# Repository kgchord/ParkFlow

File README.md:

# ParkFlow

FASTag (UHF RFID) + ANPR fusion on an on-site Edge Node for stop-free, token-free parking in India.
Vishwakarma Awards 2026-27, Stage 2 engineering package (prototype: the "ParkFlow Demo Lane").

**Status (25 Oct 2026): design stage. No hardware has been built or bench-tested yet.** Performance figures are targets or predictions to be bench-verified, unless a log in the repo shows a measured run. Billing goes to a mock NETC ledger; no real FASTag debit is attempted.

## Layout

| Folder | What is in it |
|---|---|
| `docs/` | Stage 1 concept, problem and journey, safety/FMEA, risks, roadmap, firmware notes, open decisions, references |
| `cad/openscad/` | Parametric OpenSCAD models (gantry, Edge Node enclosure, barrier, occupancy node, lane layout) |
| `cad/renders/`, `cad/dxf/`, `cad/stl/` | Preview renders, laser-cut profiles, printable parts |
| `cad/step/` | STEP interchange files generated by script from the same parameters |
| `cad/calcs/`, `cad/fea/` | Hand calculations and CalculiX/gmsh FEA decks, logs, figures |
| `cad/freecad/` | Rebuild guide and parameter spreadsheet generator for FreeCAD |
| `electronics/` | System design specification, pin map, KiCad schematic and placement-only PCB, ERC/DRC reports, diagrams |
| `firmware/` | Lane Controller (ESP32-S3) state machine and Edge Node fusion software, with host tests and logs |
| `bom/` | Priced bill of materials workbook (vendors in Delhi NCR, Bengaluru, Chennai, Mumbai) and notes |

## Reproduce

- Firmware tests: `./firmware/run_all.sh`
- FEA: `cad/fea/scripts/run_all.sh` (needs CalculiX and gmsh)
- STEP: `python3 cad/step/build_step.py` (needs CadQuery)

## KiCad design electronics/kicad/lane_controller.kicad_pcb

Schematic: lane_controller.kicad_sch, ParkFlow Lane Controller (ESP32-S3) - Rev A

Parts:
C1: 100uF 50V; CP_Elec_10x10.5
C2, C6, C13, C15, C19, C20, C22: 100nF; C_0603_1608Metric
C3, C4: 4.7uF 50V X7R; C_1210_3225Metric
C5: 6.8nF* (Cc); C_0603_1608Metric
C7, C8: 47uF 10V X5R; C_1210_3225Metric
C9: 10uF 10V; C_0805_2012Metric
C10, C11: 22uF 10V; C_0805_2012Metric
C12: 22uF; C_0805_2012Metric
C14: 1uF; C_0603_1608Metric
C18, C30, C31, C32, C33, C34, C35, C36: 10nF; C_0603_1608Metric
C21: 470uF 10V (LED bulk); CP_Elec_8x10
D1: BZT52C15 (Vgs clamp); D_SOD-123
D2: SMBJ33A; D_SMB
D3: B560C (60V 5A); D_SMC
D4: SS14 (VBUS OR); D_SMA
D5: BAT54W; D_SOD-323
D6: GREEN 0603 (3V3 OK); LED_0603_1608Metric
D7: SM712; SOT-23
D9: BAT54S (ADC clamp); SOT-23
D10, D11, D12, D13, D14, D15: 1N4148W (rev.); D_SOD-123
D16: S1M (coil flyback); D_SMA
D17: 1N4148W; D_SOD-123
D18: SS14 (5V OR); D_SMA
F1: 3A NANO2 0451003.MRL (very fast-acting); Fuse_Littelfuse-NANO2-451_453
F2: MF-R075 (0.75A hold, 60V); Fuse_Bourns_MF-RG500
J1: 24V_LOGIC_IN; TerminalBlock_Phoenix_MKDS-3-2-5.08_1x02_P5.08mm_Horizontal
J4: E-STOP NC LOOP + K1 COIL; TerminalBlock_Phoenix_MKDS-3-4-5.08_1x04_P5.08mm_Horizontal
J5: FIELD I/O 8P; TerminalBlock_Phoenix_MKDS-3-8-5.08_1x08_P5.08mm_Horizontal
J6: PSU/UPS STATUS (AC-OK, BAT-OK dry contacts to +24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; TerminalBlock_Phoenix_MKDS-3-3-5.08_1x03_P5.08mm_Horizontal
J7: RS485 RFID (A,B,0V); TerminalBlock_Phoenix_MKDS-3-3-5.08_1x03_P5.08mm_Horizontal
J8: BUZZER 24V (+, -); TerminalBlock_Phoenix_MKDS-3-2-5.08_1x02_P5.08mm_Horizontal
J9: HUB12 2x8 IDC (verify vs P10 silkscreen); IDC-Header_2x08_P2.54mm_Vertical
J10: WS2812 JST-XH 3P (B3B-XH-A); JST_XH_B3B-XH-A_1x03_P2.50mm_Vertical
J11: EDGE LINK JST-XH 5P (B5B-XH-A); JST_XH_B5B-XH-A_1x05_P2.50mm_Vertical
J12: USB-C 16P (GCT USB4105-GF-A); USB_C_Receptacle_GCT_USB4105-xx-A_16P_TopMnt_Horizontal
J13: P10 SIGN POWER 5V/3A; TerminalBlock_Phoenix_MKDS-3-2-5.08_1x02_P5.08mm_Horizontal
J14: IBT-2 LOGIC 1x8 (RPWM,LPWM,R_EN,L_EN,R_IS,L_IS,VC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; PinHeader_1x08_P2.54mm_Vertical
JP1: TERM EN; PinHeader_1x02_P2.54mm_Vertical
L1: 6.8uH Isat>=7A*; L_12x12mm_H8mm
L2: 2.2uH 3A; L_Taiyo-Yuden_NR-40xx
Q1: FQD11P06 (-60V P-FET)*; TO-252-2
Q2, Q3: 2N7002; SOT-23
Q4: IRLML0060TRPBF (60V); SOT-23
Q5: IRLML0060TRPBF; SOT-23
R1, R3, R8, R15, R16, R41, R45, R49, R53, R57, R61, R83: 10k; R_0603_1608Metric
R2, R10, R19, R20, R30, R31, R32, R78, R81: 100k; R_0603_1608Metric
R4: 200k (fsw 500 kHz); R_0603_1608Metric
R5: 10k* (Rc); R_0603_1608Metric
R6: 100k (EN/UVLO upper); R_0603_1608Metric
R7: 53.6k (Vout=5.09V); R_0603_1608Metric
R9: 453k; R_0603_1608Metric
R11, R12: 5.1k; R_0603_1608Metric
R13, R14: 22R; R_0603_1608Metric
R17, R18, R77, R80: 100R; R_0603_1608Metric
R21, R29: 1k; R_0603_1608Metric
R22: 10k (DE pull-down); R_0603_1608Metric
R23, R24: 680R fail-safe bias (DNP); R_0603_1608Metric
R25: 120R term; R_0603_1608Metric
R28: 1k* R_IS (DNP: the IBT-2 module already has 1k on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; R_0603_1608Metric
R40, R44, R48, R52, R56, R60, R82: 4.7k 1206; R_1206_3216Metric
R64: 10k (OE pull-up: sign off at reset); R_0603_1608Metric
R70, R71, R72, R73, R74, R75: 33R; R_0603_1608Metric
R76: 330R; R_0603_1608Metric
R90: 10k (EN/UVLO lower, UVLO ~13 V); R_0603_1608Metric
R91: 100R (IS_A isolation); R_0603_1608Metric
R92: 100R (IS_B isolation); R_0603_1608Metric
R93: 10k (unused A7 tie); R_0603_1608Metric
SW1: BOOT; SW_SPST_TL3342
SW2: RESET; SW_SPST_TL3342
U1: TPS54560BDDA; TI_SO-PowerPAD-8_ThermalVias
U2: TLV62569DBVR; SOT-23-5
U3: USBLC6-2SC6; SOT-23-6
U4: ESP32-S3-WROOM-1-N16R8; ESP32-S3-WROOM-1
U5: TPS3823-33DBVR (WDT 1.6 s); SOT-23-5
U6: THVD1450DR; SOIC-8_3.9x4.9mm_P1.27mm
U9: 74AHCT1G08 (R_EN = L_EN = MOT_EN & ESTOP_OK, 5 V 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; SOT-23-5
U10: 74AHCT1G08 (LPWM = CLOSE only if BEAM_CLEAR); SOT-23-5
U11, U12, U13, U14, U15, U16, U17: EL817S1(C) / PC817; SMDIP-4_W9.53mm
U18: SN74HCT245PWR (5 V, TTL inputs); TSSOP-20_4.4x6.5mm_P0.65mm
U19: 74AHCT1G08 (RPWM = OPEN request & ESTOP_OK); SOT-23-5

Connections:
/+3V3: C10.1, C11.1, C12.1, C13.1, C15.1, D9.2 (K), L2.2, R9.1, R15.1, R16.1, R21.1, R23.1, R64.2, U4.2 (3V3), U5.3 (~MR), U5.5 (VDD), U6.8 (VCC), U11.4, U12.4, U13.4, U14.4, U15.4, U16.4, U17.4
/+5V: C7.1, C8.1, C19.1, C20.1, C21.1, C22.1, D18.2 (A), J10.1, J13.1, J14.7, L1.2, R7.1, U9.5 (VCC), U10.5 (VCC), U18.1 (A->B), U18.20 (VCC), U19.5 (VCC)
/+5V_LOGIC: C9.1, D4.1 (K), D18.1 (K), U2.1 (EN), U2.4 (VIN)
/+24V: C1.1, C3.1, C4.1, D1.1 (K), D2.2 (A2), F2.1, Q1.3 (S), R2.1, R6.1, U1.2 (VIN)
/+24V_FIELD: D17.1 (K), F2.2, J4.1, J5.1, J5.7, J6.3, J8.1
/AC_OK: C34.1, R57.1, U4.21 (IO13), U15.3
/BAT_OK: C35.1, R61.1, U4.38 (IO2), U16.3
/BEAM_CLEAR: C32.1, R49.1, U4.19 (IO11), U10.2, U13.3
/BUZ_CTRL: R77.1, U4.11 (IO18)
/BUZ_G: Q5.1 (G), R77.2, R78.1
/BUZ_LO: D17.2 (A), J8.2, Q5.3 (D)
/EDGE_RX: R18.1, U4.36 (RXD0)
/EDGE_TX: R17.1, U4.37 (TXD0)
/ESP_EN: C14.1, D5.2 (A), Q2.3 (D), R15.2, SW2.1, U4.3 (EN)
/ESTOP_LOOP: D16.1 (K), J4.2, J4.3, R82.1
/ESTOP_OK: C36.1, R83.1, U4.12 (IO8), U9.2, U17.3, U19.2
/GND: C1.2, C2.2, C3.2, C4.2, C5.2, C7.2, C8.2, C9.2, C10.2, C11.2, C12.2, C13.2, C14.2, C15.2, C18.2, C19.2, C20.2, C21.2, C22.2, C30.2, C31.2, C32.2, C33.2, C34.2, C35.2, C36.2, D2.1 (A1), D3.2 (A), D6.1 (K), D7.3 (common), D9.1 (A), D10.2 (A), D11.2 (A), D12.2 (A), D13.2 (A), D14.2 (A), D15.2 (A), J1.2, J5.2, J5.8, J7.3, J9.3, J9.5, J9.7, J9.9, J9.11, J9.13, J9.15, J10.3, J11.1, J12.A1 (GND), J12.A12 (GND), J12.B1 (GND), J12.B12 (GND), J12.S1 (SHIELD), J13.2, J14.8, Q2.2 (S), Q3.2 (S), Q4.2 (S), Q5.2 (S), R1.2, R3.2, R4.2, R8.2, R10.2, R11.2, R12.2, R19.2, R20.2, R22.2, R24.2, R28.2, R30.2, R31.2, R32.2, R41.2, R45.2, R49.2, R53.2, R57.2, R61.2, R78.2, R81.2, R83.2, R90.2, R93.2, SW1.2, SW2.2, U1.7 (GND), U1.9 (GND), U2.2 (GND), U3.2 (GND), U4.1 (GND), U4.40 (GND), U4.41 (GND), U5.2 (GND), U6.5 (GND), U9.3 (GND), U10.3 (GND), U11.2, U12.2, U13.2, U14.2, U15.2, U16.2, U17.2, U18.10 (GND), U18.19 (CE), U19.3 (GND)
/GPIO0_BOOT: Q3.3 (D), R16.2, SW1.1, U4.27 (IO0)
/GPIO19_USB_DN: R14.2, U4.13 (IO19)
/GPIO20_USB_DP: R13.2, U4.14 (IO20)
/HUB_A: J9.2, R70.2
/HUB_A_3V3: U4.31 (IO38), U18.2 (A0)
/HUB_A_5: R70.1, U18.18 (B0)
/HUB_B: J9.4, R71.2
/HUB_B_3V3: U4.32 (IO39), U18.3 (A1)
/HUB_B_5: R71.1, U18.17 (B1)
/HUB_CLK: J9.8, R72.2
/HUB_CLK_3V3: U4.33 (IO40), U18.4 (A2)
/HUB_CLK_5: R72.1, U18.16 (B2)
/HUB_LAT: J9.10, R73.2
/HUB_LAT_3V3: U4.34 (IO41), U18.5 (A3)
/HUB_LAT_5: R73.1, U18.15 (B3)
/HUB_OE: J9.1, R74.2
/HUB_OE_3V3: R64.1, U4.35 (IO42), U18.6 (A4)
/HUB_OE_5: R74.1, U18.14 (B4)
/HUB_R: J9.12, R75.2
/HUB_R_3V3: U4.24 (IO47), U18.7 (A5)
/HUB_R_5: R75.1, U18.13 (B5)
/IN_ACOK: J6.1, R56.1
/IN_BATOK: J6.2, R60.1
/IN_BEAM: J5.5, R48.1
/IN_LIM_DN: J5.4, R44.1
/IN_LIM_UP: J5.3, R40.1
/IN_PRES: J5.6, R52.1
/IS_A: J14.5, R91.1
/IS_B: J14.6, R92.1
/J11_RX: J11.3, R18.2
/J11_TX: J11.2, R17.2
/K1_COIL_LO: D16.2 (A), J4.4, Q4.3 (D)
/K1_EN: R80.1, U4.25 (IO48)
/K1_G: Q4.1 (G), R80.2, R81.1
/LED_PWR_A: D6.2 (A), R21.2
/LIM_DN_OK: C31.1, R45.1, U4.18 (IO10), U12.3
/LIM_UP_OK: C30.1, R41.1, U4.17 (IO9), U11.3
/MOT_EN_MCU: R30.1, U4.7 (IO7), U9.1
/MOT_INH: J14.3, J14.4, U9.4
/MOT_IN_A: R32.1, U4.5 (IO5), U19.1
/MOT_IN_B_MCU: R31.1, U4.6 (IO6), U10.1
/MOT_IS: R28.1, R29.1, R91.2, R92.2
/MOT_ISENSE: C18.1, D9.3 (COM), R29.2, U4.39 (IO1)
/MOT_LPWM: J14.2, U10.4
/MOT_RPWM: J14.1, U19.4
/OPTO0_A: D10.1 (K), R40.2, U11.1
/OPTO1_A: D11.1 (K), R44.2, U12.1
/OPTO2_A: D12.1 (K), R48.2, U13.1
/OPTO3_A: D13.1 (K), R52.2, U14.1
/OPTO4_A: D14.1 (K), R56.2, U15.1
/OPTO5_A: D15.1 (K), R60.2, U16.1
/OPTO6_A: R82.2, U17.1
/PI_BOOT_CTRL: J11.5, Q3.1 (G), R20.1
/PI_EN_CTRL: J11.4, Q2.1 (G), R19.1
/PRESENCE: C33.1, R53.1, U4.20 (IO12), U14.3
/Q1_G: D1.2 (A), Q1.1 (G), R1.1
/RS485_A: D7.1 (A1), J7.1, R23.2, R25.1, U6.6 (A)
/RS485_B: D7.2 (A2), J7.2, JP1.2 (B), R24.1, U6.7 (B)
/RS485_DE: R22.1, U4.10 (IO17), U6.2 (~RE), U6.3 (DE)
/RS485_DI: U4.8 (IO15), U6.4 (DI)
/RS485_RO: U4.9 (IO16), U6.1 (RO)
/RS485_TERM: JP1.1 (A), R25.2
/U1_BOOT: C6.1, U1.1 (BOOT)
/U1_CC: C5.1, R5.2
/U1_COMP: R5.1, U1.6 (COMP)
/U1_EN: R6.2, R90.1, U1.3 (EN)
/U1_FB: R7.2, R8.1, U1.5 (FB)
/U1_RT: R4.1, U1.4 (RT/CLK)
/U1_SW: C6.2, D3.1 (K), L1.1, U1.8 (SW)
/U2_FB: R9.2, R10.1, U2.5 (FB)
/U2_SW: L2.1, U2.3 (SW)
/U18_A7_TIE: R93.1, U18.9 (A7)
/USB_CC1: J12.A5 (CC1), R11.1
/USB_CC2: J12.B5 (CC2), R12.1
/USB_DN: R14.1, U3.4 (I/O2)
/USB_DN_C: J12.A7 (D-), J12.B7 (D-), U3.3 (I/O2)
/USB_DP: R13.1, U3.6 (I/O1)
/USB_DP_C: J12.A6 (D+), J12.B6 (D+), U3.1 (I/O1)
/V24_SENSE: C2.1, R2.2, R3.1, U4.4 (IO4)
/VBUS: D4.2 (A), J12.A4 (VBUS), J12.A9 (VBUS), J12.B4 (VBUS), J12.B9 (VBUS), U3.5 (VBUS)
/VIN_F: F1.2, Q1.2 (D)
/VIN_RAW: F1.1, J1.1
/WDT_RST_N: D5.1 (K), U5.1 (~RESET)
/WDT_WDI: U4.22 (IO14), U5.4 (WDI)
/WS2812_3V3: U4.23 (IO21), U18.8 (A6)
/WS2812_5: R76.1, U18.12 (B6)
/WS2812_DOUT: J10.2, R76.2

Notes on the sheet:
1. 24 V INPUT PROTECTION (fuse, reverse-polarity P-FET, TVS)
2. 24 V -> 5 V BUCK (TPS54560, 5 A)
3. 5 V -> 3.3 V BUCK (TLV62569, 2 A) + USB-C
4. ESP32-S3-WROOM-1-N16R8 + RESET / BOOT / WATCHDOG / EDGE LINK
5. RS485 TO UHF RFID READER (THVD1450 + SM712)
6. H-BRIDGE: IBT-2 (BTS7960) MODULE HEADER + hardware interlocks (74AHCT1G08 @ 5 V)
7. OPTO-ISOLATED 24 V INPUTS (active-high: 24 V at the terminal = LED on = output HIGH)
8. E-STOP LOOP + CONTACTOR COIL DRIVER (firmware-independent motor cut)
9. HUB12 (P10) + WS2812 LEVEL SHIFT (74HCT245 @5 V), BUZZER
10. FIELD CONNECTORS (5.08 mm fixed screw terminals / JST-XH)
Notes: (a) Symbol MAX481E used for THVD1450DR (identical 8-pin RS485 pinout). (b) TLV62568DBV symbol used for TLV62569DBVR (same pinout). (c) 74LS245 symbol used for SN74HCT245PWR and 74LVC1G08 symbol used for the 74AHCT1G08 gates U9/U10/U19 (same pinout). (d) K1 is the external DIN contactor LC1D0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
K1 = external DIN contactor Schneider LC1D09BD (24 VDC coil); its contacts switch the +24V line to the IBT-2 module B+ (off this PCB). E-stop (BOM: ProMax 22 mm 2-pole, contacts 1 A DC) NC contact in series with the coil supply: pressing it de-energises K1 and removes motor power regardless of firm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
J5: limit switches (BOM: ME-8108) wired on the NC contact between +24V_FIELD (J5.1) and IN_LIM_x (open = limit reached or wire break -> LOW -> safe); confirm the NC terminal on the real part. IN_BEAM: the BOM through-beam receiver (Delta PS-MT5 series, PNP) drives 24 V onto IN_BEAM when the beam is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

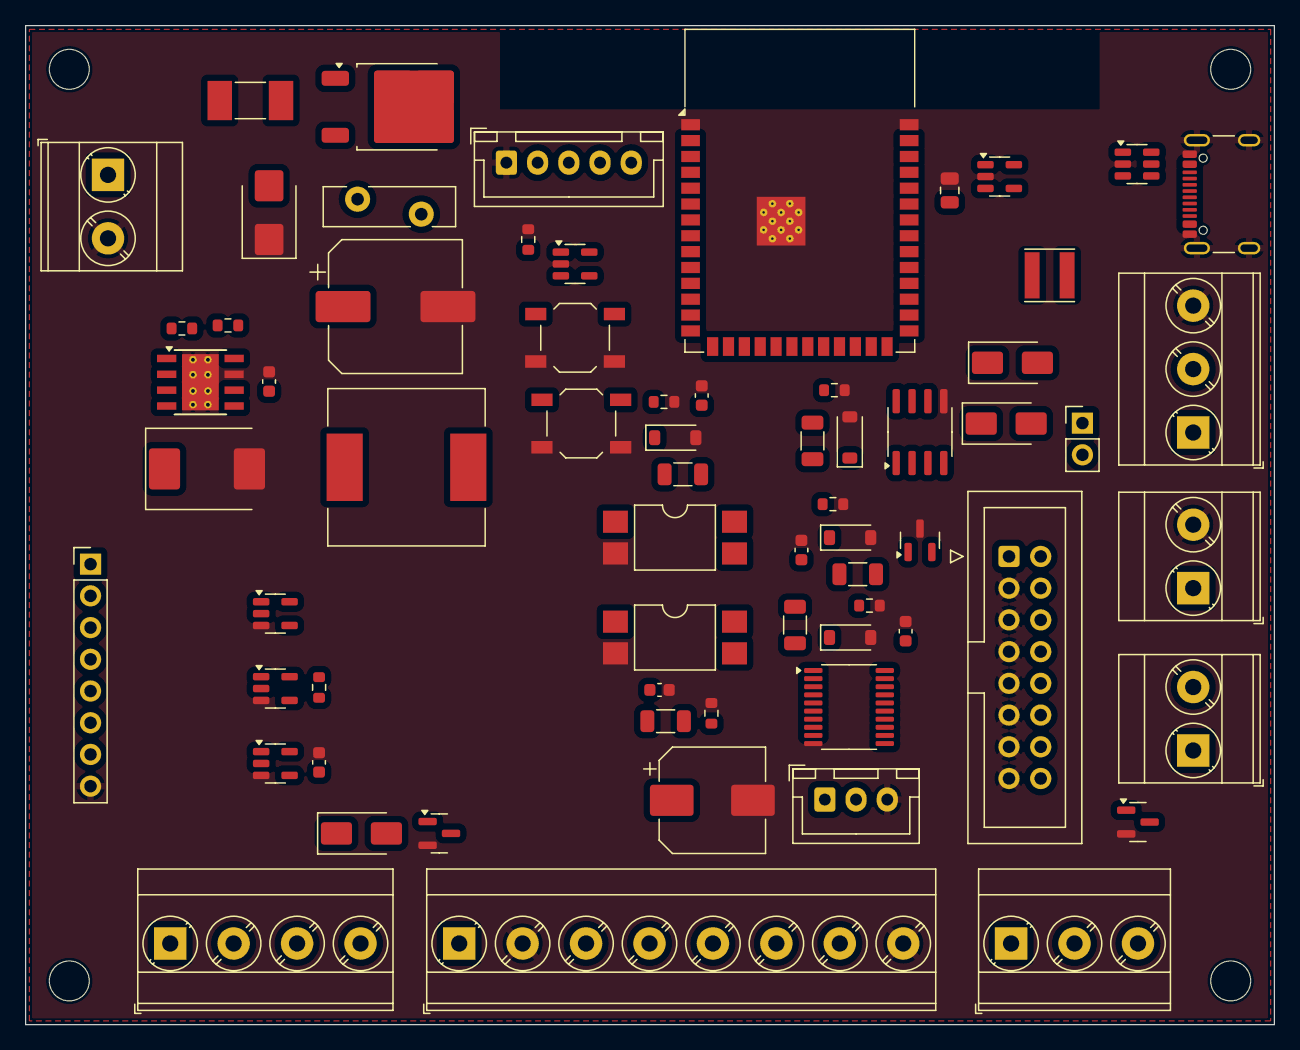
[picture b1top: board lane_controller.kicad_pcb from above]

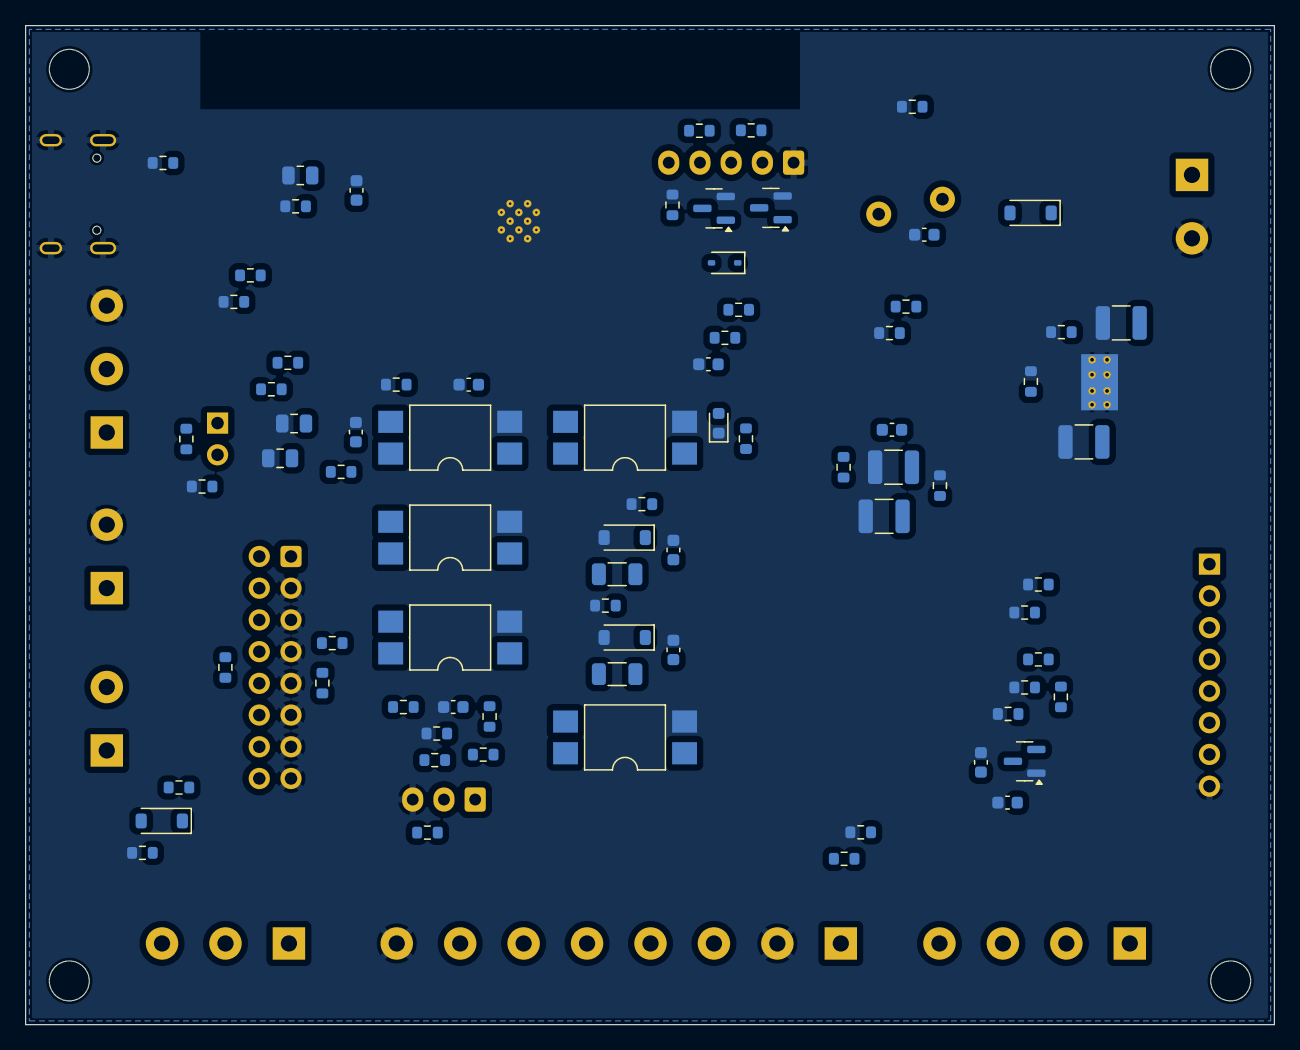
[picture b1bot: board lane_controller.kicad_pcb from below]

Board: 2 copper layers, 100.0 x 80.0 mm, 149 parts (78 on the bottom side), 104 nets, no tracks yet.

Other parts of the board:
H1, H2, H3, H4: M3; MountingHole_3.2mm_M3

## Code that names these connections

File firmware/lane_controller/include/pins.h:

// ESP32-S3-WROOM-1 pin assignment for the ParkFlow Lane Controller (Rev A).
// SOURCE OF TRUTH: electronics/tools/gen_lane_controller_sch.py, dict `esp`.
// If the schematic changes, change this file (test_pins in the host suite
// cross-checks the table below against itself for duplicates only; it cannot
// read the Python script).
#pragma once
namespace pf {
namespace pins {
constexpr int BOOT_BTN   = 0;   // GPIO0_BOOT  (also used as RE-ARM button after boot, see FIRMWARE.md)
constexpr int MOT_ISENSE = 1;   // ADC1_CH0, IBT-2 module R_IS/L_IS via R91/R92 100R + R29 1k + clamp
constexpr int BAT_OK     = 2;   // opto in, UPS battery OK (HIGH = ok)
constexpr int V24_SENSE  = 4;   // ADC1_CH3, 100k/10k divider on +24V
constexpr int MOT_IN_A   = 5;   // H-bridge half A IN (OPEN drive)
constexpr int MOT_IN_B   = 6;   // H-bridge half B IN (CLOSE drive); PCB gates it with BEAM_CLEAR (U10)
constexpr int MOT_EN     = 7;   // H-bridge INH request; PCB ANDs it with ESTOP_OK (U9)
constexpr int ESTOP_OK   = 8;   // opto in, HIGH = E-stop loop healthy
constexpr int LIM_UP_OK  = 9;   // opto in, NC switch: HIGH = NOT at limit, LOW = reached or wire break
constexpr int LIM_DN_OK  = 10;  // same polarity as LIM_UP_OK
constexpr int BEAM_CLEAR = 11;  // opto in, HIGH = beam clear (light-ON receiver); LOW = broken or cable cut
constexpr int PRESENCE   = 12;  // opto in, HIGH = occupied (ASSUMED: sensor type not fixed by schematic)
constexpr int AC_OK      = 13;  // opto in, HIGH = mains OK (PSU relay closed)
constexpr int WDT_WDI    = 14;  // TPS3823-33 WDI, toggled to kick external watchdog (1.6 s)
constexpr int RS485_DI   = 15;  // ESP TX -> THVD1450 DI
constexpr int RS485_RO   = 16;  // ESP RX <- THVD1450 RO
constexpr int RS485_DE   = 17;  // DE and /RE tied together
constexpr int BUZ_CTRL   = 18;  // 24 V piezo, low-side MOSFET, HIGH = sound
constexpr int USB_DN     = 19;  // native USB (programming)
constexpr int USB_DP     = 20;
constexpr int WS2812     = 21;  // status RGB LED (via 74HCT245 level shift)
constexpr int HUB_A      = 38;  // HUB12 via 74HCT245
constexpr int HUB_B      = 39;
constexpr int HUB_CLK    = 40;
constexpr int HUB_LAT    = 41;
constexpr int HUB_OE     = 42;  // R64 pull-up: sign blanked at reset
constexpr int HUB_R      = 47;  // HUB12 data
constexpr int K1_EN      = 48;  // contactor coil driver, HIGH = energise K1 (motor power on)
constexpr int EDGE_TX    = 43;  // UART0 TXD0 -> Edge Node (R17 100R)
constexpr int EDGE_RX    = 44;  // UART0 RXD0 <- Edge Node (R18 100R)
}  // namespace pins
}  // namespace pf

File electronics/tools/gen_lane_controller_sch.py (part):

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P('Device', 'D_Schottky', 'D4', 'SS14 (VBUS OR)', (150, 290), {'A': 'VBUS', 'K': '+5V_LOGIC'}, fp='Diode_SMD:D_SMA')
P('Device', 'D_Schottky', 'D18', 'SS14 (5V OR)', (150, 275), {'A': '+5V', 'K': '+5V_LOGIC'}, fp='Diode_SMD:D_SMA')
P('power', 'PWR_FLAG', '#FLG05', 'PWR_FLAG', (185, 230), {'1': '+5V_LOGIC'})
R('R13', '22R', (170, 300), 'USB_DP', 'GPIO20_USB_DP', rot=90)
R('R14', '22R', (170, 312), 'USB_DN', 'GPIO19_USB_DN', rot=90)

# ------------------------------------------------------------------ 4. ESP32-S3
esp = {
    '3V3': '+3V3', 'GND': 'GND', 'EN': 'ESP_EN',
    'IO0': 'GPIO0_BOOT', 'IO1': 'MOT_ISENSE', 'IO2': 'BAT_OK', 'IO3': 'NC', 'IO4': 'V24_SENSE',
    'IO5': 'MOT_IN_A', 'IO6': 'MOT_IN_B_MCU', 'IO7': 'MOT_EN_MCU', 'IO8': 'ESTOP_OK', 'IO9': 'LIM_UP_OK',
    'IO10': 'LIM_DN_OK', 'IO11': 'BEAM_CLEAR', 'IO12': 'PRESENCE', 'IO13': 'AC_OK', 'IO14': 'WDT_WDI',
    'IO15': 'RS485_DI', 'IO16': 'RS485_RO', 'IO17': 'RS485_DE', 'IO18': 'BUZ_CTRL',
    'IO19': 'GPIO19_USB_DN', 'IO20': 'GPIO20_USB_DP', 'IO21': 'WS2812_3V3',
    'IO35': 'NC', 'IO36': 'NC', 'IO37': 'NC',
    'IO38': 'HUB_A_3V3', 'IO39': 'HUB_B_3V3', 'IO40': 'HUB_CLK_3V3', 'IO41': 'HUB_LAT_3V3', 'IO42': 'HUB_OE_3V3',
    'IO45': 'NC', 'IO46': 'NC', 'IO47': 'HUB_R_3V3', 'IO48': 'K1_EN',
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C('C13', '100nF', (312, 55), '+3V3', 'GND')
R('R15', '10k', (270, 60), '+3V3', 'ESP_EN')
C('C14', '1uF', (270, 85), 'ESP_EN', 'GND')
R('R16', '10k', (270, 110), '+3V3', 'GPIO0_BOOT')
P('Switch', 'SW_Push', 'SW1', 'BOOT', (270, 135), {'1': 'GPIO0_BOOT', '2': 'GND'}, fp='Button_Switch_SMD:SW_SPST_TL3342')
P('Switch', 'SW_Push', 'SW2', 'RESET', (270, 150), {'1': 'ESP_EN', '2': 'GND'}, fp='Button_Switch_SMD:SW_SPST_TL3342')
# external watchdog TPS3823-33 (WDI 1.6 s): RESET pulls EN low through Schottky (diode-OR with RC / Pi)
P('ParkFlow', 'TPS3823-33', 'U5', 'TPS3823-33DBVR (WDT 1.6 s)', (420, 60),
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R('R17', '100R', (420, 110), 'EDGE_TX', 'J11_TX', rot=90)
R('R18', '100R', (420, 125), 'EDGE_RX', 'J11_RX', rot=90)
P('Device', 'Q_NMOS_GSD', 'Q2', '2N7002', (430, 150), {'G': 'PI_EN_CTRL', 'S': 'GND', 'D': 'ESP_EN'}, fp='Package_TO_SOT_SMD:SOT-23')
P('Device', 'Q_NMOS_GSD', 'Q3', '2N7002', (460, 150), {'G': 'PI_BOOT_CTRL', 'S': 'GND', 'D': 'GPIO0_BOOT'}, fp='Package_TO_SOT_SMD:SOT-23')
R('R19', '100k', (430, 180), 'PI_EN_CTRL', 'GND')
R('R20', '100k', (460, 180), 'PI_BOOT_CTRL', 'GND')
P('Connector_Generic', 'Conn_01x05', 'J11', 'EDGE LINK JST-XH 5P (B5B-XH-A)', (470, 110),
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R('R23', '680R fail-safe bias (DNP)', (345, 245), '+3V3', 'RS485_A')
R('R24', '680R fail-safe bias (DNP)', (345, 290), 'RS485_B', 'GND')
R('R25', '120R term', (365, 268), 'RS485_A', 'RS485_TERM')
P('Jumper', 'Jumper_2_Open', 'JP1', 'TERM EN', (390, 268), {'A': 'RS485_TERM', 'B': 'RS485_B'}, fp='Connector_PinHeader_2.54mm:PinHeader_1x02_P2.54mm_Vertical')
P('Diode', 'SM712_SOT23', 'D7', 'SM712', (420, 268), {'A1': 'RS485_A', 'A2': 'RS485_B', 'common': 'GND'}, fp='Package_TO_SOT_SMD:SOT-23')
P('Connector', 'Screw_Terminal_01x03', 'J7', 'RS485 RFID (A,B,0V)', (460, 268),
  {'1': 'RS485_A', '2': 'RS485_B', '3': 'GND'}, fp='TerminalBlock_Phoenix:TerminalBlock_Phoenix_MKDS-3-3-5.08_1x03_P5.08mm_Horizontal')
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P('Connector_Generic', 'Conn_01x08', 'J14', 'IBT-2 LOGIC 1x8 (RPWM,LPWM,R_EN,L_EN,R_IS,L_IS,VCC,GND)', (530, 60),
  {'1': 'MOT_RPWM', '2': 'MOT_LPWM', '3': 'MOT_INH', '4': 'MOT_INH', '5': 'IS_A', '6': 'IS_B', '7': '+5V', '8': 'GND'},
  fp='Connector_PinHeader_2.54mm:PinHeader_1x08_P2.54mm_Vertical')
R('R28', '1k* R_IS (DNP: the IBT-2 module already has 1k on each IS pin)', (640, 175), 'MOT_IS', 'GND', )
R('R91', '100R (IS_A isolation)', (600, 160), 'IS_A', 'MOT_IS', rot=90)
R('R92', '100R (IS_B isolation)', (600, 172), 'IS_B', 'MOT_IS', rot=90)
R('R29', '1k', (660, 160), 'MOT_IS', 'MOT_ISENSE', rot=90)
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R('R81', '100k', (130, 415), 'K1_G', 'GND')
# E-stop healthy sense (fail-safe: loop broken -> ESTOP_OK low)
R('R82', '4.7k 1206', (150, 365), 'ESTOP_LOOP', 'OPTO6_A', fp='Resistor_SMD:R_1206_3216Metric')
P('Isolator', 'PC817', 'U17', 'EL817S1(C) / PC817', (180, 380), {'1': 'OPTO6_A', '2': 'GND', '3': 'ESTOP_OK', '4': '+3V3'}, fp='Package_DIP:SMDIP-4_W9.53mm')
R('R83', '10k', (215, 400), 'ESTOP_OK', 'GND')
C('C36', '10nF', (228, 400), 'ESTOP_OK', 'GND')
s.note('K1 = external DIN contactor Schneider LC1D09BD (24 VDC coil); its contacts switch the +24V line to the IBT-2 module B+ (off this PCB). E-stop (BOM: ProMax 22 mm 2-pole, contacts 1 A DC)\n'
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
